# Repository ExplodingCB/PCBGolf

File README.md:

> **Engineering handoff — incomplete and not submitted.** Start with [HANDOFF.md](HANDOFF.md). The latest 45 × 37 mm, four-layer BGA100 checkpoint is in [work-in-progress/](work-in-progress/README.md), including an assembly STEP. It has **184 remaining pad-group connections and zero physical DRC errors**. Work stopped at the owner's request; all subagents and routing jobs are stopped. The root project is an earlier placement baseline.

<div align="center">
<h1>PCBGolf Challenge</h1>
<h3>How small can you make this PCBA?</h3>
<h3>
  <a href="https://comma.ai/leaderboard#pcbgolf_challenge">Leaderboard</a>
  <span> · </span>
  <a href="https://comma.ai/jobs">comma.ai/jobs</a>
  <span> · </span>
  <a href="https://discord.comma.ai">Discord</a>
  <span> · </span>
  <a href="https://x.com/comma_ai">X</a>
</h3>
</div>

## The Board

The schematic is loosely based on [our panda jungle v2](https://www.comma.ai/shop/panda-jungle), a development and debugging board for comma devices and pandas. This version includes:

* 12V DC input with onboard 5V and 3.3V supplies
* Four [OBD-C](https://github.com/commaai/hardware/blob/master/harness/OBD-C.sch.pdf) device ports with individually controlled power and current monitoring
* Four CAN transceivers and ignition simulation circuitry
* A USB hub and USB-C host connection
* An STM32H725 microcontroller and microSD card slot
* A push button and status LEDs

Explore in your browser with KiCanvas: [PCB layout](https://kicanvas.org/?github=https%3A%2F%2Fgithub.com%2Fcommaai%2FPCBGolf%2Fblob%2Fmaster%2Fpcbgolf.kicad_pcb).

Schematics: [Power](https://kicanvas.org/?github=https%3A%2F%2Fgithub.com%2Fcommaai%2FPCBGolf%2Fblob%2Fmaster%2Fpcbgolf.kicad_sch) · [Microcontroller](https://kicanvas.org/?github=https%3A%2F%2Fgithub.com%2Fcommaai%2FPCBGolf%2Fblob%2Fmaster%2Fpcbgolf_2.kicad_sch) · [USB & microSD](https://kicanvas.org/?github=https%3A%2F%2Fgithub.com%2Fcommaai%2FPCBGolf%2Fblob%2Fmaster%2Fpcbgolf_3.kicad_sch) · [CAN](https://kicanvas.org/?github=https%3A%2F%2Fgithub.com%2Fcommaai%2FPCBGolf%2Fblob%2Fmaster%2Fpcbgolf_4.kicad_sch) · [OBD-C ports](https://kicanvas.org/?github=https%3A%2F%2Fgithub.com%2Fcommaai%2FPCBGolf%2Fblob%2Fmaster%2Fpcbgolf_5.kicad_sch)

## The Challenge

Your goal is to make the most compact, efficient board that retains the same interfaces and functionality as the original design. The lowest score wins.

<p align="center">
  <picture>
    <source media="(prefers-color-scheme: dark)" srcset="./assets/score-dark.svg">
    
  </picture>
</p>

### Rules

* The bare PCB must be fully manufacturable by JLCPCB.
* It must be possible to actually assemble the PCBA.
* The assembled product must work and be usable.
* Mating connectors must remain mechanically and electrically compatible.

### Prize

Lowest score on the [leaderboard](https://comma.ai/leaderboard#pcbgolf_challenge) by **October 12, 2026** wins **$1,000 cash**.

## Submission

Submit a `.zip` file containing your finalized KiCad project and a STEP file of the final assembly [here](https://forms.gle/US88Hg7UR6bBuW3BA).
Competitive scores will be posted on the [leaderboard](https://comma.ai/leaderboard#pcbgolf_challenge) after review. Multiple submissions allowed.

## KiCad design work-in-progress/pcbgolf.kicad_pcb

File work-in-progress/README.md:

# PCBGolf engineering checkpoint

Updated September 14, 2026. **Incomplete, not fabrication-ready, and not submitted.** Work stopped at the owner's request. Start with [../HANDOFF.md](../HANDOFF.md) for exact artifact provenance, remaining blockers, toolchain and proposed continuation plan. All subagents and routing jobs are stopped.

## Current design

- 45 × 37 mm outline, four copper layers, 1.6 mm PCB thickness, 239 components.
- STM32H725VGH6 in an 8 × 8 mm TFBGA100 package, with corresponding schematic and GPIO changes.
- Project-local schematic symbols, footprints and 3D models are included. Open `pcbgolf.kicad_pro` here; the repository-root project is an earlier placement baseline.
- This snapshot is the last completed `via400` routing result: 2,715 track segments and 484 through vias. `pcbgolf.merge.json` records the initial merge only.
- `assembly.step` contains the board and all 236 populated component models. All 239 component placements were compared and exactly match this latest PCB; only routing changed after the STEP export. Final fabrication artifacts should be exported again.

## Known blockers

- `net-groups.json` reports **184 missing connections between connected pad groups across 113 nets**.
- `drc.json` contains **zero physical error records and zero hole-spacing warnings**. Unconnected items and other warnings still require completion and review.
- `connectivity-parity.json` passes all five schematic sheets: 239 components, zero component or pin/net differences.
- `usb-reference-audit.json` verifies all 17 ground return vias connect to both original inner layers. One small reference-copper gap remains flagged among 223 USB segments.
- CAN bus routing is partly integrated; connector and transceiver branches still require connections. The older isolated trial is documented separately in `../reports/can-routing-trial.md`.
- Power distribution, current capacity, final manufacturing checks and firmware/hardware validation remain unfinished. Some vias require filled and capped via-in-pad processing.

## Preserved work

Engineering scripts and reports are in `../scripts/` and `../reports/`. Reports describe their named candidates. `routing-source.*` and `routing-handoff/via400*` preserve the exact source, DSN, SES, hash and log for the latest output. `small-via-trial.*` is a separate older 190-open experiment with 130 reduced signal vias; do not replace the latest main board with it. Other experiments and installed toolchains remain local and are excluded from Git. **No six-layer conversion was implemented.**

Firmware source changes and the local build driver are in `../firmware/pcbgolf/`. Bootstub and application compiled and linked locally; neither was hardware-tested. No flashable binaries are included in this checkpoint.

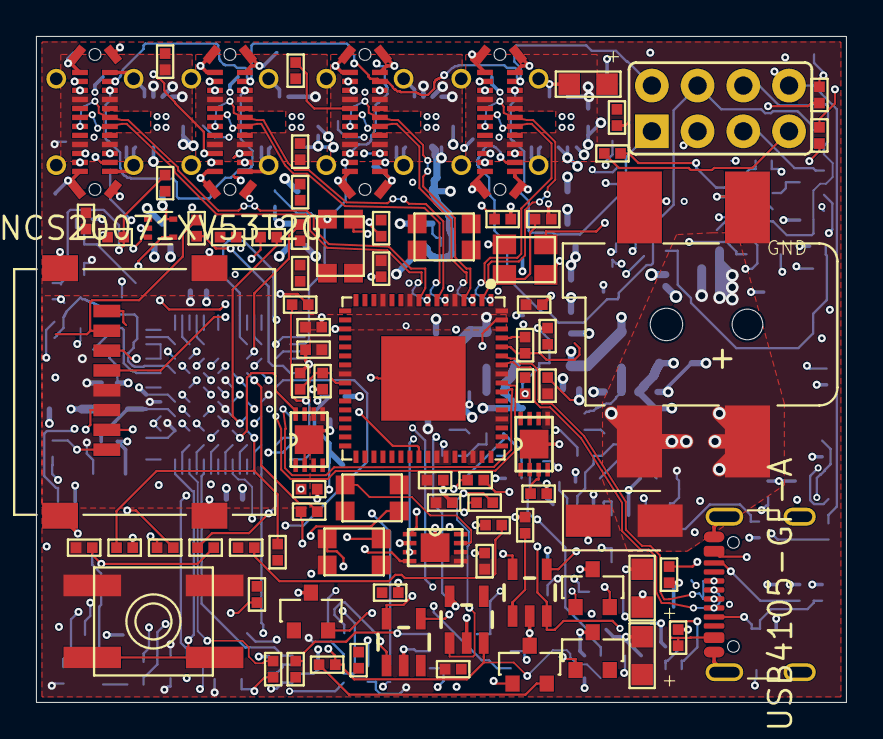
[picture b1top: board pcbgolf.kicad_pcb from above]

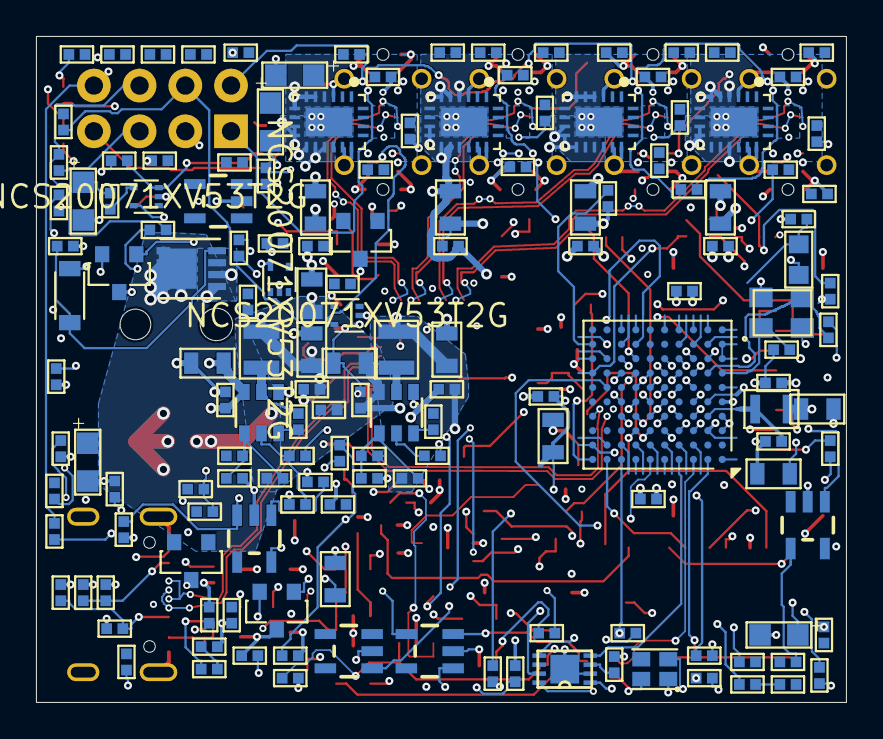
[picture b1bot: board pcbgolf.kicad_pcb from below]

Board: 4 copper layers, 45.0 x 37.0 mm, 239 parts (154 on the bottom side), 191 nets.

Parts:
C1, C3, C8, C12, C13, C15, C19, C20, C21: 10uF; 0805-C
C2, C4, C5, C7, C9, C11, C16, C18, C22, C23, C24, C26, C27, C30, C31, C35, C36, C38, C39, C40, C41, C42, C43, C44, C45, C46, C47, C48, C49: 100nF; 0402-C
C6, C10: DNP; 0402-C
C14, C17, C28, C32: 12pF; 0402-C
C25: 220pF; 0402-C
C29, C33, C34, C37: 10u; 0402-C
C50, C51, C52, C53: 10u; 0805-C
D1: SMAJ16CA; D_SMA
D2: DIODEDB2W40100L; SOD-123F
J1: DCBARRELSMT; PJ-002AH-SMT-TR
J2: MICRO_SD-0472192001; 0472192001
J3: USB4105-GF-A; USB_C_Receptacle_GCT_USB4105-xx-A_16P_TopMnt_Horizontal
J4: CAN; 2X04
J5, J6, J7, J8: USB-C-FEMALEGCT; USB-C-FEMALE-VERT-GCT
L1, L2: 3u3; L-1008
L3: L-US-L2; 0603-L
L4: 2u2; 0806
L5, L6, L7, L8: ACT1210D_CHOKE; CHOKE-3.2X2.5
LED1: CREE-RGB-CLMVC
LED2: CAN0; CHIPLED
LED3: CAN1; CHIPLED
LED4: CAN2; CHIPLED
LED5: CAN3; CHIPLED
LED6, LED7, LED8, LED9: CH1_PWR; CHIPLED
LED10, LED11, LED12, LED13, LED14, LED15, LED16, LED17: LED-CC-GREEN-RED-AM23ESG; SOT23-3
Q1: SIS427-VI; PP-1212-8
Q2, Q3, Q4, Q5, Q6, Q7, Q8, Q9: NFET-DUAL-COMMON-SOURCE-QS5K2; SOT23-5
R1, R3, R7, R8, R9, R11, R12, R28, R29, R30, R31, R32, R33, R34, R35, R36, R37, R44, R45, R50, R51, R53, R54, R56, R57, R59, R60, R70, R71, R72, R73, R78, R79, R80, R81, R98, R99, R100, R101, R102, R103, R104, R105, R122, R123, R124, R125: 10k; 0402-R
R2, R21, R23, R90, R92, R94, R96, R114, R116, R118, R120: 1k; 0402-R
R4: 31k2; 0402-R
R10: 52k3; 0402-R
R13, R14, R15, R16, R17, R18, R19, R20, R24, R25, R52, R55, R58, R61: 100k; 0402-R
R22, R62, R63, R64, R65: 2k7; 0402-R
R26: 1M; 0402-R
R27: 12k; 0402-R
R38, R39, R40, R41, R42, R43: 0R; 0402-R
R46, R47, R48, R49: 60; 0402-R
R66, R67, R68, R69: 28k; 0402-R
R74, R75, R76, R77: 3k3; 0402-R
R82, R83, R84, R85, R86, R87, R88, R89, R91, R93, R95, R97, R106, R107, R108, R109, R110, R111, R112, R113, R115, R117, R119, R121: 100; 0402-R
SW1: SPST-2-4PIN; EVQ-Q2
U1, U2: AP62300; SOT23-6
U3: STM32H725VGH6; STM32H725VGH6_TFBGA100
U4: USB2517; QFN64-9X9
U5, U6, U7, U8: MCP2542FDT-E/MNY; TDFN8_2X3MC_MCH
U9, U10, U11, U12: NCS20071XV53T2G; SOT-553
U13, U14, U15, U16: TPS25944A; WQFN20
Y1: 25MHz; XTAL-3.2X2.5
Y2: 24MHz; XTAL-3.2X2.5

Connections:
+3V3: C6.2, C7.1, C8.1, C19.1, C20.1, C23.1, C24.1, C26.1, C27.1, C30.2, C31.2, C37.1, C42.1, C43.1, C44.1, C45.1, J2.4 (VDD), L1.2, L3.1, LED1.U1 (COM+), R4.1, R11.1, R28.1, R29.1, R30.1, R33.1, R34.1, R35.1, R36.1, R37.1, SW1.B (S), SW1.B' (S1), U3.C2, U3.D6, U3.E1, U3.E5, U3.E8, U3.F6, U4.5 (VDDA33), U4.10 (VDDA33), U4.13 (CFG_SEL2), U4.24 (VDD33CR), U4.42 (CFG_SEL1), U4.43 (RESET_N), U4.46 (VDD33), U4.52 (VDDA33), U4.57 (VDDA33), U4.64 (VDD33PLL), U5.5 (VIO), U6.5 (VIO), U7.5 (VIO), U8.5 (VIO)
+5V: C1.1, C2.1, C10.2, C11.1, C12.1, C13.1, C38.1, C39.1, C40.1, C41.1, L2.2, R1.1, R10.2, R52.2, R55.2, R58.2, R61.2, U1.3 (IN), U5.3 (VDD), U6.3 (VDD), U7.3 (VDD), U8.3 (VDD)
+12V: C3.1, C5.1, C46.1, C47.1, C48.1, C49.1, C50.1, C51.1, C52.1, C53.1, D2.1 (C), Q1.1 (S), Q1.2 (S), Q1.3 (S), R7.1, U2.3 (IN), U9.5, U10.5, U11.5, U12.5, U13.9 (VIN), U13.10 (VIN), U13.11 (VIN), U13.12 (VIN), U13.13 (VIN), U14.9 (VIN), U14.10 (VIN), U14.11 (VIN), U14.12 (VIN), U14.13 (VIN), U15.9 (VIN), U15.10 (VIN), U15.11 (VIN), U15.12 (VIN), U15.13 (VIN), U16.9 (VIN), U16.10 (VIN), U16.11 (VIN), U16.12 (VIN), U16.13 (VIN)
BTN: R12.2, SW1.A, SW1.A' (P1), U3.A2, U3.A5
CAN0_EN: U3.B5, U5.8 (STBY)
CAN0_H: J4.2, J5.A2 (TX1+), J6.A2 (TX1+), J7.A2 (TX1+), J8.A2 (TX1+), L5.4, R46.2, R50.1
CAN0_L: J4.1, J5.A3 (TX1-), J6.A3 (TX1-), J7.A3 (TX1-), J8.A3 (TX1-), L5.3, R46.1, R51.1
CAN0_RX: U3.A4, U5.4 (RXD)
CAN0_TX: U3.E3, U5.1 (TXD)
CAN1_EN: U3.B6, U6.8 (STBY)
CAN1_H: J4.4, J5.A11 (RX2+), J6.A11 (RX2+), J7.A11 (RX2+), J8.A11 (RX2+), L6.4, R47.2, R53.1
CAN1_L: J4.3, J5.A10 (RX2-), J6.A10 (RX2-), J7.A10 (RX2-), J8.A10 (RX2-), L6.3, R47.1, R54.1
CAN1_RX: U3.A6, U6.4 (RXD)
CAN1_TX: U3.D4, U6.1 (TXD)
CAN2_EN: U3.C6, U7.8 (STBY)
CAN2_H: J4.6, J5.B2 (TX2+), J6.B2 (TX2+), J7.B2 (TX2+), J8.B2 (TX2+), L7.4, R48.2, R56.1
CAN2_L: J4.5, J5.B3 (TX2-), J6.B3 (TX2-), J7.B3 (TX2-), J8.B3 (TX2-), L7.3, R48.1, R57.1
CAN2_RX: U3.H9, U7.4 (RXD)
CAN2_TX: U3.H10, U7.1 (TXD)
CAN3_EN: U3.C5, U8.8 (STBY)
CAN3_H: J4.8, J5.B11 (RX1+), J6.B11 (RX1+), J7.B11 (RX1+), J8.B11 (RX1+), L8.4, R49.2, R59.1
CAN3_L: J4.7, J5.B10 (RX1-), J6.B10 (RX1-), J7.B10 (RX1-), J8.B10 (RX1-), L8.3, R49.1, R60.1
CAN3_RX: U3.K8, U8.4 (RXD)
CAN3_TX: U3.J8, U8.1 (TXD)
CH1_D_N: J5.A7 (D-A), J5.B7 (D-B), U4.1 (USBDN1_DM)
CH1_D_P: J5.A6 (D+A), J5.B6 (D+B), U4.2 (USBDN1_DP)
CH1_IMON: R70.2, U3.H4, U13.19 (IMON)
CH1_PWR_EN: U3.G3, U13.14 (EN)
CH1_SBU1: J5.A8 (SBU1), R19.2, R90.2, R91.2
CH1_SBU1_IGN: Q2.1 (G1), R78.1, R83.2, U3.C7
CH1_SBU1_RELAY: Q2.3 (G2), R82.2, R98.2, U3.B8
CH1_SBU2: J5.B8 (SBU2), R20.2, R114.2, R115.2
CH1_SBU2_IGN: Q6.1 (G1), R102.1, R107.2, U3.A8
CH1_SBU2_RELAY: Q6.3 (G2), R106.2, R122.2, U3.B7
CH2_D_N: J6.A7 (D-A), J6.B7 (D-B), U4.3 (USBDN2_DM)
CH2_D_P: J6.A6 (D+A), J6.B6 (D+B), U4.4 (USBDN2_DP)
CH2_IMON: R71.2, U3.K5, U14.19 (IMON)
CH2_PWR_EN: U3.J2, U14.14 (EN)
CH2_SBU1: J6.A8 (SBU1), R15.2, R92.2, R93.2
CH2_SBU1_IGN: Q3.1 (G1), R79.1, R85.2, U3.D7
CH2_SBU1_RELAY: Q3.3 (G2), R84.2, R99.2, U3.A7
CH2_SBU2: J6.B8 (SBU2), R13.2, R116.2, R117.2
CH2_SBU2_IGN: Q7.1 (G1), R103.1, R109.2, U3.J9
CH2_SBU2_RELAY: Q7.3 (G2), R108.2, R123.2, U3.J10
CH3_D_N: J7.A7 (D-A), J7.B7 (D-B), U4.6 (USBDN3_DM)
CH3_D_P: J7.A6 (D+A), J7.B6 (D+B), U4.7 (USBDN3_DP)
CH3_IMON: R72.2, U3.K4, U15.19 (IMON)
CH3_PWR_EN: U3.K1, U15.14 (EN)
CH3_SBU1: J7.A8 (SBU1), R17.2, R94.2, R95.2
CH3_SBU1_IGN: Q4.1 (G1), R80.1, R87.2, U3.A1
CH3_SBU1_RELAY: Q4.3 (G2), R86.2, R100.2, U3.H7
CH3_SBU2: J7.B8 (SBU2), R18.2, R118.2, R119.2
CH3_SBU2_IGN: Q8.1 (G1), R104.1, R111.2, U3.H8
CH3_SBU2_RELAY: Q8.3 (G2), R110.2, R124.2, U3.H5
CH4_D_N: J8.A7 (D-A), J8.B7 (D-B), U4.8 (USBDN4_DM)
CH4_D_P: J8.A6 (D+A), J8.B6 (D+B), U4.9 (USBDN4_DP)
CH4_IMON: R73.2, U3.J3, U16.19 (IMON)
CH4_PWR_EN: U3.K2, U16.14 (EN)
CH4_SBU1: J8.A8 (SBU1), R16.2, R96.2, R97.2
CH4_SBU1_IGN: Q5.1 (G1), R81.1, R89.2, U3.G7
CH4_SBU1_RELAY: Q5.3 (G2), R88.2, R101.2, U3.G8
CH4_SBU2: J8.B8 (SBU2), R14.2, R120.2, R121.2
CH4_SBU2_IGN: Q9.1 (G1), R105.1, R113.2, U3.B4
CH4_SBU2_RELAY: Q9.3 (G2), R112.2, R125.2, U3.C4
GND: C1.2, C2.2, C3.2, C5.2, C7.2, C8.2, C11.2, C12.2, C13.2, C14.2, C15.2, C16.2, C17.2, C18.2, C19.2, C20.2, C21.2, C22.2, C23.2, C24.2, C25.2, C26.2, C27.2, C28.2, C29.2, C30.1, C31.1, C32.2, C33.2, C34.2, C35.1, C36.1, C37.2, C38.2, C39.2, C40.2, C41.2, C42.2, C43.2, C44.2, C45.2, C46.2, C47.2, C48.2, C49.2, C50.2, C51.2, C52.2, C53.2, D1.1, J1.GND, J1.GNDBREAK, J2.6 (VSS), J2.G1 (GND), J2.G2 (GND), J2.G3 (GND), J2.G4 (GND), J3.A1, J3.A12, J3.B1, J3.B12, J3.SH, J5.A1 (GND), J5.A12 (GND), J5.B1 (GND), J5.B12 (GND), J5.S1 (SHIELDA), J5.S2 (SHIELDA), J5.S3 (SHIELDA), J5.S4 (SHIELDA), J5.S11 (SHIELDB), J5.S12 (SHIELDB), J5.S13 (SHIELDB), J5.S14 (SHIELDB), J6.A1 (GND), J6.A12 (GND), J6.B1 (GND), J6.B12 (GND), J6.S1 (SHIELDA), J6.S2 (SHIELDA), J6.S3 (SHIELDA), J6.S4 (SHIELDA), J6.S11 (SHIELDB), J6.S12 (SHIELDB), J6.S13 (SHIELDB), J6.S14 (SHIELDB), J7.A1 (GND), J7.A12 (GND), J7.B1 (GND), J7.B12 (GND), J7.S1 (SHIELDA), J7.S2 (SHIELDA), J7.S3 (SHIELDA), J7.S4 (SHIELDA), J7.S11 (SHIELDB), J7.S12 (SHIELDB), J7.S13 (SHIELDB), J7.S14 (SHIELDB), J8.A1 (GND), J8.A12 (GND), J8.B1 (GND), J8.B12 (GND), J8.S1 (SHIELDA), J8.S2 (SHIELDA), J8.S3 (SHIELDA), J8.S4 (SHIELDA), J8.S11 (SHIELDB), J8.S12 (SHIELDB), J8.S13 (SHIELDB), J8.S14 (SHIELDB), LED2.C, LED3.C, LED4.C, LED5.C, LED6.C, LED7.C, LED8.C, LED9.C, LED10.3 (C), LED11.3 (C), LED12.3 (C), LED13.3 (C), LED14.3 (C), LED15.3 (C), LED16.3 (C), LED17.3 (C), Q2.2 (S), Q3.2 (S), Q4.2 (S), Q5.2 (S), Q6.2 (S), Q7.2 (S), Q8.2 (S), Q9.2 (S), R2.1, R3.2, R8.2, R9.2, R12.1, R25.1, R27.1, R31.2, R32.2, R44.2, R45.2, R66.1, R67.1, R68.1, R69.1, R70.1, R71.1, R72.1, R73.1, R78.2, R79.2, R80.2, R81.2, R98.1, R99.1, R100.1, R101.1, R102.2, R103.2, R104.2, R105.2, R122.1, R123.1, R124.1, R125.1, U1.1 (GND), U2.1 (GND), U3.C1, U3.D1, U3.D5, U3.E7, U3.F5, U3.H2, U4.19 (TEST), U4.PAD (VSS), U5.2 (VSS), U5.PAD (EPAD), U6.2 (VSS), U6.PAD (EPAD), U7.2 (VSS), U7.PAD (EPAD), U8.2 (VSS), U8.PAD (EPAD), U9.2, U10.2, U11.2, U12.2, U13.3 (PGTH), U13.15 (OVP), U13.16 (GND), U13.PAD (GND), U14.3 (PGTH), U14.15 (OVP), U14.16 (GND), U14.PAD (GND), U15.3 (PGTH), U15.15 (OVP), U15.16 (GND), U15.PAD (GND), U16.3 (PGTH), U16.15 (OVP), U16.16 (GND), U16.PAD (GND), Y1.2 (3), Y1.4 (3), Y2.2 (3), Y2.4 (3)
HUB_SCL: R30.2, U3.K7, U4.41 (SCL)
HUB_SDA: R28.2, U3.J7, U4.40 (SDA)
LED_B: R23.2, U3.A3
LED_G: R22.2, U3.B3
LED_R: R21.2, U3.C3
unnamed: D2.2 (A), Q1.4 (G), R2.2
unnamed: D1.2, J1.PWR1, Q1.5 (D), Q1.6 (D), Q1.7 (D), Q1.8 (D), Q1.9 (D)
unnamed: J2.2 (CD/DAT3), R36.2, R41.2
unnamed: J2.5 (CLK), R43.2
unnamed: J2.3 (CMD), R37.2, R42.2
unnamed: J2.7 (DAT0), R33.2, R38.2
unnamed: J2.8 (DAT1), R34.2, R39.2
unnamed: J2.1 (DAT2), R35.2, R40.2
unnamed: J3.A5, R31.1, R32.1
unnamed: J3.B5, R44.1, R45.1
unnamed: J5.A4 (VBUS), J5.A9 (VBUS), J5.B4 (VBUS), J5.B9 (VBUS), R74.1, U13.4 (VOUT), U13.5 (VOUT), U13.6 (VOUT), U13.7 (VOUT), U13.8 (VOUT)
unnamed: J6.A4 (VBUS), J6.A9 (VBUS), J6.B4 (VBUS), J6.B9 (VBUS), R75.1, U14.4 (VOUT), U14.5 (VOUT), U14.6 (VOUT), U14.7 (VOUT), U14.8 (VOUT)
unnamed: J7.A4 (VBUS), J7.A9 (VBUS), J7.B4 (VBUS), J7.B9 (VBUS), R76.1, U15.4 (VOUT), U15.5 (VOUT), U15.6 (VOUT), U15.7 (VOUT), U15.8 (VOUT)
unnamed: J8.A4 (VBUS), J8.A9 (VBUS), J8.B4 (VBUS), J8.B9 (VBUS), R77.1, U16.4 (VOUT), U16.5 (VOUT), U16.6 (VOUT), U16.7 (VOUT), U16.8 (VOUT)
unnamed: LED1.U4 (B-), R23.1
unnamed: LED1.U3 (G-), R22.1
unnamed: LED1.U2 (R-), R21.1
unnamed: LED2.A, R62.2
unnamed: LED3.A, R63.2
unnamed: LED4.A, R64.2
unnamed: LED5.A, R65.2
unnamed: LED6.A, R74.2
unnamed: LED7.A, R75.2
unnamed: LED8.A, R76.2
unnamed: LED9.A, R77.2
unnamed: LED10.2 (AG), R82.1
unnamed: LED10.1 (AR), R83.1
unnamed: LED11.2 (AG), R84.1
unnamed: LED11.1 (AR), R85.1
unnamed: LED12.2 (AG), R86.1
unnamed: LED12.1 (AR), R87.1
unnamed: LED13.2 (AG), R88.1
unnamed: LED13.1 (AR), R89.1
unnamed: LED14.2 (AG), R106.1
unnamed: LED14.1 (AR), R107.1
unnamed: LED15.2 (AG), R108.1
unnamed: LED15.1 (AR), R109.1
unnamed: LED16.2 (AG), R110.1
unnamed: LED16.1 (AR), R111.1
unnamed: LED17.2 (AG), R112.1
unnamed: LED17.1 (AR), R113.1
unnamed: Q2.5 (D1), R90.1
unnamed: Q2.4 (D2), R91.1
unnamed: Q3.5 (D1), R92.1
unnamed: Q3.4 (D2), R93.1
unnamed: Q4.5 (D1), R94.1
unnamed: Q4.4 (D2), R95.1
unnamed: Q5.5 (D1), R96.1
unnamed: Q5.4 (D2), R97.1
unnamed: Q6.5 (D1), R114.1
unnamed: Q6.4 (D2), R115.1
unnamed: Q7.5 (D1), R116.1
unnamed: Q7.4 (D2), R117.1
unnamed: Q8.5 (D1), R118.1
unnamed: Q8.4 (D2), R119.1
unnamed: Q9.5 (D1), R120.1
unnamed: Q9.4 (D2), R121.1
unnamed: R62.1, U9.4
unnamed: R63.1, U10.4
unnamed: R64.1, U11.4
unnamed: R65.1, U12.4
unnamed: C4.1, U1.6 (BST)
unnamed: R1.2, U1.5 (EN)
unnamed: C6.1, R3.1, R4.2, U1.4 (FB)
unnamed: C4.2, L1.1, U1.2 (SW)
unnamed: C9.1, U2.6 (BST)
unnamed: R7.2, R8.1, U2.5 (EN)
unnamed: C10.1, R9.1, R10.1, U2.4 (FB)
unnamed: C9.2, L2.1, U2.2 (SW)
unnamed: R17.1, U3.F3
unnamed: R18.1, U3.F1
unnamed: R19.1, U3.F4
unnamed: R20.1, U3.G4
unnamed: R11.2, U3.D3
unnamed: R13.1, U3.H3
unnamed: R14.1, U3.G5
unnamed: R15.1, U3.K3
unnamed: R16.1, U3.J4
unnamed: C14.1, U3.G1, Y1.1
unnamed: C17.1, U3.G2, Y1.3 (2)
unnamed: R27.2, U4.63 (RBIAS)
unnamed: R29.2, U4.45 (SUSP_IND)
unnamed: R24.1, R25.2, U4.44 (VBUS_DET)
unnamed: C33.1, C35.2, U4.25 (VDD18)
unnamed: C34.1, C36.2, U4.62 (VDD18PLL)
unnamed: C28.1, R26.2, U4.61 (XTAL1), Y2.1
unnamed: C32.1, R26.1, U4.60 (XTAL2), Y2.3 (2)
unnamed: L5.1, U5.7 (CANH)
unnamed: L5.2, U5.6 (CANL)
unnamed: L6.1, U6.7 (CANH)
unnamed: L6.2, U6.6 (CANL)
unnamed: L7.1, U7.7 (CANH)
unnamed: L7.2, U7.6 (CANL)
unnamed: L8.1, U8.7 (CANH)
unnamed: L8.2, U8.6 (CANL)
unnamed: R50.2, U9.1
unnamed: R51.2, R52.1, U9.3
unnamed: R53.2, U10.1
unnamed: R54.2, R55.1, U10.3
unnamed: R56.2, U11.1
unnamed: R57.2, R58.1, U11.3
unnamed: R59.2, U12.1
unnamed: R60.2, R61.1, U12.3
unnamed: R66.2, U13.17 (ILIM)
unnamed: R67.2, U14.17 (ILIM)
unnamed: R68.2, U15.17 (ILIM)
unnamed: R69.2, U16.17 (ILIM)
SD_CLK: R43.1, U3.A10
SD_CMD: R42.1, U3.A9
SD_D0: R38.1, U3.G10
SD_D1: R39.1, U3.F9
SD_D2: R40.1, U3.B10
SD_D3: R41.1, U3.B9
STM_D_N: U3.D10, U4.55 (USBDN7_DM)
STM_D_P: U3.D9, U4.56 (USBDN7_DP)
USB_D_N: J3.A7, J3.B7, U4.58 (USBUP_DM)
USB_D_P: J3.A6, J3.B6, U4.59 (USBUP_DP)
VBUS: C29.1, J3.A4, J3.A9, J3.B4, J3.B9, R24.2
VDDA: C22.1, L3.2, U3.H1, U3.J1
VDDLDO: C15.1, C16.1, C18.1, C21.1, L4.1, U3.D8, U3.E2, U3.E6, U3.F7, U3.G6
VLXSMPS: C25.1, L4.2, U3.D2

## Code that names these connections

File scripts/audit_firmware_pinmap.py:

"""Check firmware GPIO/ADC selections against schematic allocation and ST pin data."""
import hashlib,json,re
from pathlib import Path
ROOT=Path(__file__).resolve().parents[1]
header=ROOT/'firmware/pcbgolf/pcbgolf_bga100.h'
allocation=ROOT/'reports/mcu-bga100-feasibility.json'
official=ROOT/'reports/mcu-100pin-functions.json'
text=header.read_text();pins=json.loads(allocation.read_text())['ball_assignments']
by_function={p['function']:p for p in pins};st=json.loads(official.read_text())['STM32H725VGHx']['pins']
arrays=dict(re.findall(r'gpio_t (\w+)\[\] = \{(.*?)\};',text,re.S));checks=[]
for array,suffix in {'power_pins':'PWR_EN','sbu1_ignition_pins':'SBU1_IGN','sbu1_relay_pins':'SBU1_RELAY',
                     'sbu2_ignition_pins':'SBU2_IGN','sbu2_relay_pins':'SBU2_RELAY','can_enable_pins':None}.items():
    rows=re.findall(r'GPIO([A-Z]),\s*(\d+)',arrays[array]);assert len(rows)==4,array
    for i,(bank,pin) in enumerate(rows):
        gpio='P'+bank+pin;expected=f'CH{i+1}_{suffix}' if suffix else f'CAN{i}_EN'
        actual=by_function[gpio];assert actual['net']==expected,(array,i,actual,expected)
        checks.append({'kind':'GPIO','array':array,'channel':i+1,**actual})
adc_expected={
    'imon_channels':['CH1_IMON','CH2_IMON','CH3_IMON','CH4_IMON'],
    'sbu1_channels':['Net-(U3-PC2_C)','Net-(U3-PF9)','Net-(U3-PC0)','Net-(U3-PF10)'],
    'sbu2_channels':['Net-(U3-PC3_C)','Net-(U3-PF7)','Net-(U3-PC1)','Net-(U3-PF8)'],
}
for array,expected in adc_expected.items():
    body=re.search(r'const adc_signal_t '+array+r'\[\] = \{(.*?)\};',text,re.S).group(1)
    channels=re.findall(r'PCBGOLF_ADC\((ADC\d),\s*(\d+)\)',body);assert len(channels)==4
    for i,((adc,channel),net) in enumerate(zip(channels,expected)):
        row=next(p for p in pins if p['net']==net);signal=adc+'_INP'+channel
        official_pin=next(v for v in st.values() if v['position']==row['ball'])
        assert signal in official_pin['signals'],(array,i,signal,official_pin)
        checks.append({'kind':'ADC','array':array,'channel':i+1,'signal':signal,**row})
for gpio,net,signal in [('PB8','CAN0_RX','FDCAN1_RX'),('PB9','CAN0_TX','FDCAN1_TX'),
                       ('PB5','CAN1_RX','FDCAN2_RX'),('PB6','CAN1_TX','FDCAN2_TX'),
                       ('PD12','CAN2_RX','FDCAN3_RX'),('PD13','CAN2_TX','FDCAN3_TX'),
                       ('PB12','CAN3_RX','FDCAN2_RX'),('PB13','CAN3_TX','FDCAN2_TX')]:
    row=by_function[gpio];assert row['net']==net
    official_pin=next(v for v in st.values() if v['position']==row['ball'])
    assert signal in official_pin['signals']
    checks.append({'kind':'CAN alternate function','signal':signal,**row})
assert by_function['PE5']['net']=='BTN'
result={'status':'GPIO and ADC allocation checks passed; hardware not tested','checks':checks,
        'sources':{str(p.relative_to(ROOT)):hashlib.sha256(p.read_bytes()).hexdigest() for p in (header,allocation,official)},
        'limitations':['Checks the allocation documented by schematic parity and official ST pin data.',
                       'Does not validate firmware timing, all peripherals, power-up behavior or electrical operation.']}
(ROOT/'firmware/pcbgolf/pinmap.json').write_text(json.dumps(result,indent=2))
print(json.dumps({'checked_gpio_adc_can_assignments':len(checks),'status':result['status']}))
